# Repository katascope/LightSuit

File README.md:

# KataTracks
The KataTracks system is three parts: The KataTracks software, the LightSuit, and the LightSuitAngel device.

## KataTracks

The KataTracks Application provides remote Bluetooth Low Energy (BLE) control over multiple LightSuits.

## LightSuit

Parts:
* BTF-LIGHTING WS2812B RGB 5050SMD Individual Addressable LED
* BTF-LIGHTING 3 Pin Electrical Connector 22AWG IP65 Male Female Connector
* Two-sided Velcro strip attached to suits
* Adhesive Velctro strip attached to LED strips
* Rubberized suit hole

Each LightSuit is a series of individually controlled addressable LED strips and LightSuitAngel. Velcro strips are attached to clothing, then to led strips. The velcro holds the strips together and connect at ends through 3-wire BTF connectors into the LightSuitAngel.

## LightSuitAngel
The LightSuitAngel devices provides 8-channels of control of LightSuit control. A 3d-printed case covers an Arduino Nano BLE device, using NeoPixel to run micro-second timed preprogrammed tracks.

Parts
* Arduino Nano BLE
* BTF-LIGHTING WS2812B RGB 5050SMD Individual Addressable LED
* BTF-LIGHTING 3 Pin Electrical Connector 22AWG IP65 Male Female Connector
* LM2596S LM2596 Buck Converter 3A DC-DC 3-40V to 1.5-35v DC Voltage Regulator 
* 1000uF 50V Capacitor
* XT60 connector
* 25pcs DIP IC Chip Socket Adaptor
* M3 screws

Other simpler 1-channel devices can also be used with BTF splitters.

In combination, the KataTracks system allows for multiple time-synchronized led light-suits to be used for performance dance.

[Show Usage](https://www.youtube.com/watch?v=vVwiPTvP0F0)

Abandoned ideas:
* Using EL wire, too monochrome of effects.
* Using IMU for colors, too unpredictable during dance.
* Using regular Arduino Nano, Bluetooth modules cumbersome to attach.
* Using Arduino Nano IOT, timing was flaky.
* Playing music to theater, theater will have to provide sound.
* JST 3-wires, connectors have no tension or bend protection.

KataTracks is under the [MIT License](https://opensource.org/licenses/MIT)

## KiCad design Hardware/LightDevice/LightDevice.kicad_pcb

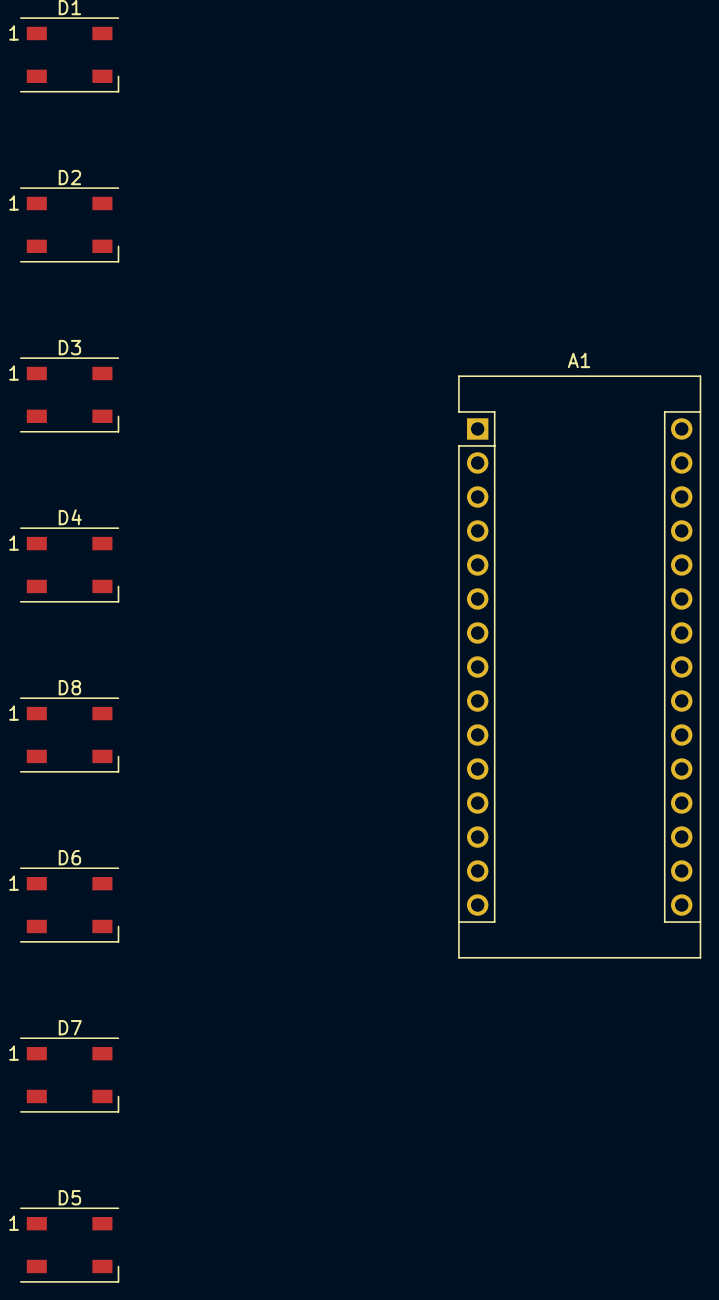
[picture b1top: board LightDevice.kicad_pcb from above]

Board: 2 copper layers, 9 parts (0 on the bottom side), 10 nets, no tracks yet.

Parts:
A1: Arduino_Nano_v3.x; Arduino_Nano
D1, D2, D3, D4, D5, D6, D7, D8: WS2812B; LED_WS2812B_PLCC4_5.0x5.0mm_P3.2mm

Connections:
+5V: A1.27 (+5V), D1.3 (VSS), D2.3 (VSS), D3.3 (VSS), D4.3 (VSS), D5.3 (VSS), D6.3 (VSS), D7.3 (VSS), D8.3 (VSS)
GND: A1.29 (GND), D1.1 (VDD), D2.1 (VDD), D3.1 (VDD), D4.1 (VDD), D5.1 (VDD), D6.1 (VDD), D7.1 (VDD), D8.1 (VDD)
unnamed: A1.6 (D3), D1.4 (DIN)
unnamed: A1.7 (D4), D2.4 (DIN)
unnamed: A1.8 (D5), D3.4 (DIN)
unnamed: A1.9 (D6), D4.4 (DIN)
unnamed: A1.10 (D7), D5.4 (DIN)
unnamed: A1.11 (D8), D6.4 (DIN)
unnamed: A1.12 (D9), D7.4 (DIN)
unnamed: A1.13 (D10), D8.4 (DIN)

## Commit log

2022-07-01 Big initial commit
2022-07-01 Testout
2022-07-26 Undo bad change to default leds
2022-07-28 Addition of TrackConfig files, Removal of track decoding
2022-07-28 Track linear checks
2022-11-29 Katatracks upgrades, Lightsuit prep for Foxbutt project
2022-12-06 Display tweaks
2022-12-16 Emotional Space for Mree
2022-12-16 test
2022-12-16 tests
2022-12-16 Serial reader
2022-12-16 Pree
2022-12-16 Pree adjust
2022-12-16 Removed files
2022-12-17 Updates to stabilize on jetson builds
2022-12-17 Sync up
2022-12-18 This is a change
2022-12-20 Servo functionality
2022-12-20 Working servos
2022-12-20 Servo poses
2022-12-20 Foxen dia extension rename
2022-12-23 FoxTracks implementation
2022-12-23 Mree standing up now
2022-12-24 Smoothlerp
2022-12-24 Foxen advancements, more poses and lerping of poses
2022-12-24 Combined oled + serial core for mree to build on
2022-12-25 Working sleep to wake state, with autorun on jetson
2022-12-25 Mree update with sound/state/serial/video coordination
2022-12-25 Sync it all up
2022-12-25 Cleanup 2
2022-12-25 Working ble control of Mree
2022-12-25 About 20 bluetooth teleoperation poses for katatracks and mree
2022-12-27 Pree readiness
2022-12-28 Prees ble id
2022-12-28 sync
2023-01-01 Xree image
2023-01-01 BG images
2023-01-01 notes update
2023-01-02 Mree boot startup files
2023-01-02 notes
2023-01-02 Updates for pree
2023-01-02 Pree 3.7 readiness
2023-01-02 Ui updates
2023-01-02 Config readiness
2023-01-02 Proper Pree & Mree settings
2023-01-03 UI fixes and sync with code
2023-01-03 Wave update
2023-01-03 Timed lerp and wave animation
2023-01-04 Nonblocking serial read
2023-01-04 Pose DB
2023-01-04 Upgrades to allow pose storage
2023-01-04 Sound updates
2023-01-04 More sounds!
2023-01-05 Gamepad controller class for ps2 controller
2023-01-06 Joystick functionality
2023-01-06 Game controller use
2023-01-06 Double controller update
2023-01-06 Double controllers working
2023-01-06 Hannibal's dog sounds
2023-01-08 Full sounds
2023-01-09 Network call updates
2023-01-09 Servo updates
2023-01-10 New Mree ID
2023-01-11 New sounds
2023-01-11 confused sound
2023-01-11 xree sounds
2023-01-11 Auto power
2023-01-11 upgrades for ppl count display
2023-01-16 Select from controllers
2023-01-22 Selection upgrades
2023-01-22 Controller selection
2023-01-25 Arduino state upgrades
2023-01-25 Rect functions
2023-01-26 Make autonomous mode more responsive
2023-01-27 Lamp updates
2023-01-27 Autonomous mode upgrades
2023-01-28 Faster responses and cleaner output for xree
2023-01-28 Much faster iterations, "stable" serial
2023-01-28 Fix for oddity in bootup
